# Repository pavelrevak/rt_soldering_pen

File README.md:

# RT soldering pen

![oled4]

[Manual]

This firmware is for my project [RT soldering pen](https://hackaday.io/project/18899-rt-soldering-pen)

You can buy HW at [Tindie](https://www.tindie.com/products/vlk/rt-soldering-pen/)

## Building and flashing

### Requirements

- [`arm-gcc`](https://developer.arm.com/open-source/gnu-toolchain/gnu-rm/downloads)
- [`cmake`](https://cmake.org/download/)
- `make` or [`ninja`](https://github.com/ninja-build/ninja)
- STM flashing SW and HW (ST-Link/V2 or any ST dev-kit, like Discovery or Nucleo board)

Building is possible on Linux, Mac and also on Windows

### Getting source

```sh
git clone --recursive https://github.com/pavelrevak/rt_soldering_pen.git
cd rt_soldering_pen
```

### Building

```sh
mkdir _build
cd _build
cmake -D CMAKE_TOOLCHAIN_FILE=../cmake/arm-none-eabi.cmake -D CMAKE_BUILD_TYPE=Release ..
make
```

### Flashing

Connect ST-Link or other SWD programmer:

#### HW v0.3

- G : GND
- C : SWCLK
- D : SWDIO

#### HW v1.0

- C : SWCLK
- G : GND
- D : SWDIO

If you have installed [pystlink](https://github.com/pavelrevak/pystlink) and is in search path just type:

```sh
make flash
```

If you have another flashing utility you can generate hex of binary file:

```sh
make srec
```

or building also support other targets `hex` and `bin`

Final files are saved in `_build` folder

[manual]: doc/MANUAL.md "Manual"
[oled4]: doc/oled4.png "Screenshot"

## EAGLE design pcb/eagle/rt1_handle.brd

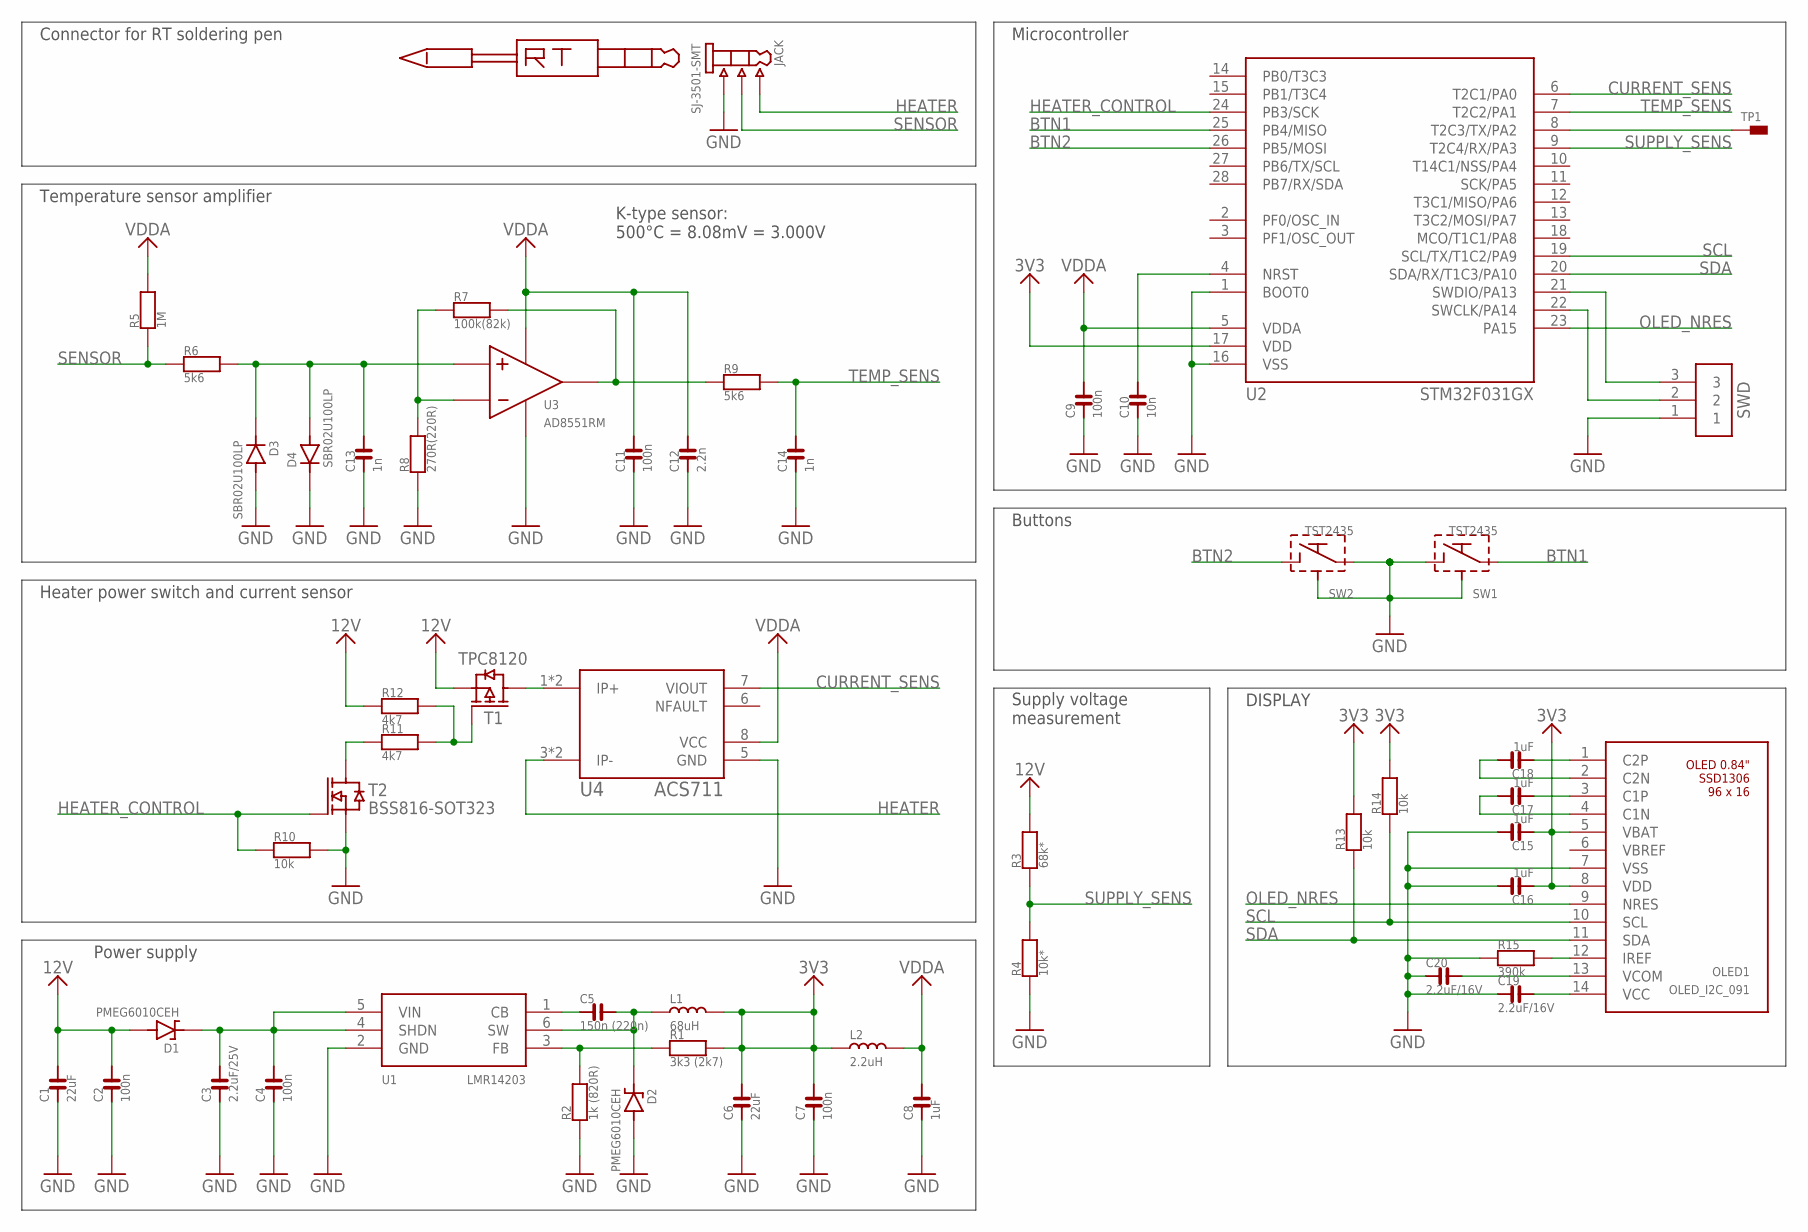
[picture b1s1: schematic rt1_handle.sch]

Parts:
C1: 22uF; 1206
C2, C4, C7, C9, C11: 100n; 0402
C3: 2.2uF/25V; 0805
C5: 150n (220n); 0402
C6: 22uF; 0805
C8, C15, C16, C17, C18: 1uF; 0603
C10: 10n; 0402
C12: 2.2n; 0603
C13, C14: 1n; 0402
C19, C20: 2.2uF/16V; 0603
D1, D2: PMEG6010CEH; SOD123F
D3, D4: SBR02U100LP; DFN1006
JACK: SJ-3501-SMT
L1: 68uH; 1717
L2: 2.2uH; 0805
OLED1: OLED_I2C_091
R1: 3k3 (2k7); 0402
R2: 1k (820R); 0402
R3: 68k*; 0402
R4: 10k*; 0402
R5: 1M; 0402
R6, R9: 5k6; 0402
R7: 100k(82k); 0402
R8: 270R(220R); 0402
R10, R13, R14: 10k; 0402
R11, R12: 4k7; 0402
R15: 390k; 0402
RT: RT-1
SW1, SW2: TST2435
SWD: PINHEAD1X3X; PIN1X3
T1: TPC8120; SOIC8
T2: BSS816-SOT323; SOT23
TP1: TEST_PAD15X60; SMD_15_60
U1: LMR14203; SOT23-6
U2: STM32F031GX; UFQFPN28
U3: AD8551RM; MSOP8
U4: ACS711; SOIC8

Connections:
3V3: C6.2, C7.2, C15.1, C16.1, L1.2, L2.1, OLED1.5 (VBAT), OLED1.8 (VDD), R1.2, R13.2, R14.2, U2.17 (VDD)
12V: C1.2, C2.2, D1.A, R3.2, R12.1, T1.1 (S), T1.2 (S), T1.3 (S)
12V_DC: C3.2, C4.2, D1.C, U1.4 (SHDN), U1.5 (VIN)
BTN1: SW1.1, U2.25 (PB4/MISO)
BTN2: SW2.2, U2.26 (PB5/MOSI)
C1N: C17.2, OLED1.4 (C1N)
C1P: C17.1, OLED1.3 (C1P)
C2N: C18.2, OLED1.2 (C2N)
C2P: C18.1, OLED1.1 (C2P)
CURRENT_SENS: U2.6 (T2C1/PA0), U4.7 (VIOUT)
DEBUG_OUT: TP1.TP, U2.8 (T2C3/TX/PA2)
GND: C1.1, C2.1, C3.1, C4.1, C6.1, C7.1, C8.1, C9.1, C10.1, C11.1, C12.1, C13.1, C14.1, C15.2, C16.2, C19.1, C20.1, D2.A, D3.A, D4.C, JACK.1, JACK.5 (1), OLED1.7 (VSS), R2.1, R4.1, R8.1, R10.2, R15.1, SW1.2, SW1.EP1 (SHIELD), SW1.EP2 (SHIELD), SW2.1, SW2.EP1 (SHIELD), SW2.EP2 (SHIELD), SWD.1, T2.2 (S), U1.2 (GND), U2.1 (BOOT0), U2.16 (VSS), U3.4 (V-), U4.5 (GND)
HEATER: JACK.2, JACK.4 (2), U4.3 (IP-), U4.4 (IP-)
HEATER_CONTROL: R10.1, T2.1 (G), U2.24 (PB3/SCK)
HEATER_PWR: T1.5 (D), T1.6 (D), T1.7 (D), T1.8 (D), U4.1 (IP+), U4.2 (IP+)
IREF: OLED1.12 (IREF), R15.2
NRST: C10.2, U2.4 (NRST)
OLED_NRES: OLED1.9 (NRES), U2.23 (PA15)
POWER_SWITCH: R11.2, R12.2, T1.4 (G)
POWER_SWITCH_LOW: R11.1, T2.3 (D)
SCL: OLED1.10 (SCL), R14.1, U2.19 (SCL/TX/T1C2/PA9)
SDA: OLED1.11 (SDA), R13.1, U2.20 (SDA/RX/T1C3/PA10)
SENSOR: JACK.3, R5.1, R6.1
SENSOR_FEEDBACK: R7.1, R8.2, U3.2 (IN-)
SENSOR_IN: C13.2, D3.C, D4.A, R6.2, U3.3 (IN+)
SENSOR_OUT: R7.2, R9.1, U3.6 (OUT)
SUPPLY_CB: C5.1, U1.1 (CB)
SUPPLY_FB: R1.1, R2.2, U1.3 (FB)
SUPPLY_SENS: R3.1, R4.2, U2.9 (T2C4/RX/PA3)
SWDCLK: SWD.2, U2.22 (SWCLK/PA14)
SWDIO: SWD.3, U2.21 (SWDIO/PA13)
SWOUT: C5.2, D2.C, L1.1, U1.6 (SW)
TEMP_SENS: C14.2, R9.2, U2.7 (T2C2/PA1)
VCC: C19.2, OLED1.14 (VCC)
VCOM: C20.2, OLED1.13 (VCOM)
VDDA: C8.2, C9.2, C11.2, C12.2, L2.2, R5.2, U2.5 (VDDA), U3.7 (V+), U4.8 (VCC)

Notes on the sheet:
K-type sensor: 500°C = 8.08mV = 3.000V
SWD
Power supply
Heater power switch and current sensor
Temperature sensor amplifier
Connector for RT soldering pen
Microcontroller
DISPLAY
Supply voltage measurement
Buttons

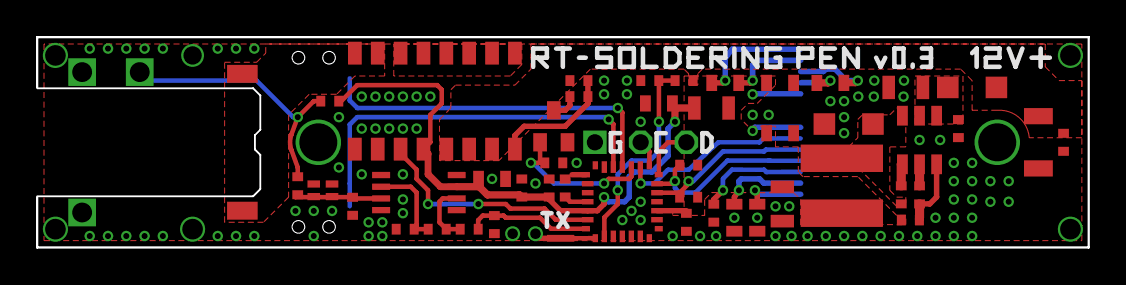
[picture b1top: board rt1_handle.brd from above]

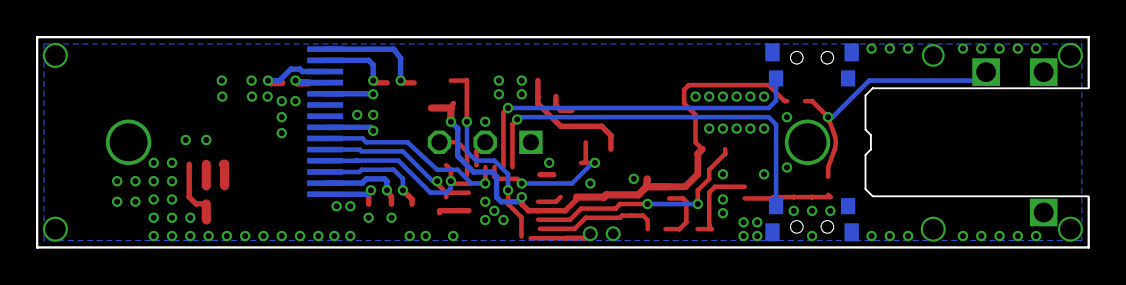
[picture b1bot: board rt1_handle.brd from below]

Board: 2 copper layers, 58.4 x 11.7 mm, 54 parts (3 on the bottom side), 36 nets.

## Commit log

2018-02-24 initial import
2018-03-10 removed pure_virtual_stub, moved button class to lib, moved analog values calculation to board.adc
2018-03-10 removed interrupt for adc dma
2018-03-18 improved handling buttons
2018-03-18 class with presets
2018-05-12 separated screen drawing
2018-05-23 improved naming
2018-05-27 flash using bin (pystlink has small bug with unaligned sections), added cmake target for size
2018-05-30 pragma once
2018-06-16 heating state machine separated from main
2018-06-17 bugfixes - heating is now working
2018-06-17 implemented diagnostics, added docstring
2018-06-17 rearanged code
2018-06-18 added RT TIP diagnostic
2018-06-18 moved heating and preset to src folder
2018-06-18 cleaned preset module
2018-06-18 cleaned screen/main
2018-06-19 fifo docstring update, namespace is lowercase
2018-06-19 updated namespaces
2018-06-20 rewrited stream and printing on display with stringstream
2018-06-20 updated ostream: removed recursive algo, changed types for fonts, ...
2018-06-20 added text width measurement, bugfix in draw_char
2018-06-20 removed unused fonts
2018-06-20 compensated current sensor to increase accuracy
2018-06-20 returned back unused fonts, compiler optimisations remove unused fonts
2018-06-22 support for additional screens
2018-06-22 added info screen
2018-06-22 moved heat processes from main.cpp into heating.hpp
2018-06-22 cleanup
2018-06-22 added io as submodule
2018-06-22 locked submodule to v0.0.20180622
2018-06-23 Create LICENSE
2018-06-23 README
2018-06-28 cleaned board/ADC module
2018-06-29 ADC: code cleaning
2018-06-29 ADC: small code refactoring
2018-06-29 heating: code refactoring and cleaning (no functionality changed)
2018-06-30 moved display init seqeuence into flash
2018-06-30 optimized drawing of info screen (this code need to rework)
2018-06-30 added undervoltage limit to limit heating power if batery has too low voltage (actually is set to 4.3V)
2018-06-30 working versions are marked with '+' like v0.0.1+
2018-06-30 added watchdog
2018-07-01 add magic word before framebuffer to easy find framebuffer in memory and take screenshots
2018-07-02 optimalized FIFO for 2^n items
2018-07-02 fixed issue with current compensation
2018-07-05 removed debugging (not used actually, can be added later, if needed)
2018-07-06 added manual
2018-07-06 corrected naming of variables with to
2018-07-06 moved manual into doc
2018-07-06 added screenshots
2018-07-06 updated doc with screenshots
2018-07-07 added simple script for creating screenshots over SWD/StLink debugger
2018-07-08 screenshot generator: configurable border
2018-07-11 improved info screen handling
2018-07-11 other improvement of info screen handling
2018-07-12 added script for testing buttons on HW without connected display
2018-07-13 fixed long buttons press
2018-07-21 basic support for Fahrenheits, one block of FLASH memory used as nonvolatile for settings with vear leveling optimizations, optimized info screen, added option to swtich degree F or C
2018-07-23 added option for advanced screen, now is default screen simple (show only preset and measured temperature) and switching to advanced screen is by menu option
2018-07-24 left-handed mode
2018-07-24 renamed info screen to menu
2018-07-24 updated documentation
2018-07-24 updated doc
2018-07-24 increased version to v0.1.0
2018-07-27 reduced binary size by removing unused fonts and unused characters (size is reduced for about 2KB)
2018-07-29 Updated manual
2018-07-29 linker script for 16KB MCU
2018-07-29 detecting shortcut on RT TIP (this state is still not processed to protect RT tip)
2018-08-03 new version of io
2018-08-03 updated Readme.md (clone with recursive)
2018-08-07 increased current limit for heater from 6A to 9A, now it will work at 18V supply
2018-08-08 updated .gitignore
2018-08-08 added minmax library
2018-08-08 added overheat limit (to 500 degree Celsius), in case of overheat will be immediatelly switched into standby + dissable heating if is standby mode
2018-08-08 increased minimum set-point temperature to 50 degree C, use minmax lib, added const to methods and code cleaning
2018-08-08 heating: added const, removed unused constant
2018-08-08 show overheat info on display (in simple mode show OH)
2018-08-08 rewrited PID, changed some modifications of PID and changed constants, now is faster heating, smaller overshot, faster reaction during soldering, .. but there is still room for improvements
2018-08-08 simple mode: in standby if temperature is more than 50 degree Celsius will temperature blink
2018-08-09 saving preset temperatures
2018-08-09 v0.2.0
2018-08-12 added used eagle libraries
2018-08-12 added schematic pdf + renamed folder
2018-08-12 pdf: schematic + pcb
2018-09-03 fixed warnings Wconversion, Wold-style-cast and Wcast-align
2018-09-03 fixed warnings Wsign-conversion
2018-09-03 fixed warnings Wshadow
2018-09-03 fixed warnings Wlogical-op
2018-09-03 updated version v0.2.0+
2018-09-04 fixed warnings Wsuggest-override
2018-09-07 removed unnecessary .cpp files
2018-09-07 updated io
2018-09-08 added dependencies comments into screenshot maker
2018-09-08 better power bargraph in simple main screen
2018-10-19 added missing mosfet library
2019-01-09 updated io to new version
2019-01-09 bugfixes for gcc-8
2019-09-22 added support for HW v1.0 (with automatic detection HW revision) + update to new io
2019-09-26 v0.3.0
2019-10-05 renamed screen ID INFO to MENU
2019-10-05 added Thermocouple type-D characteristic
2019-10-05 updated buttons testing script to exit when both buttons are pressed longer than 1s
2019-10-06 increased temperature range for HW v1.0
2019-10-06 Display control improvemenets - Display DIM after 2 minutes after inactivity - Display OFF after 15 minutes - Settings for higher brightness
2019-10-06 added schematic for hw v1.0
2019-10-06 added TOOD
2019-10-06 v0.4.0
2020-03-09 moved flash to drv
2020-03-09 updated names for constants
2020-03-09 added missing include
2020-03-09 moved eagle folder
2020-03-09 moved watchdog to drv
2021-01-20 Add "high power" setting
    Adds new selectable menu item to settings that is a boolean "high power" setting. When off, this will limit power output via heating.hpp to 40W. When on, it will limit power output via heating.hpp to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
2021-01-20 Add High Power menu item
    Adds a selectable boolean setting called "high power" beneath the "left handed" menu item. Changing this in the menu will modify the HIGH_POWER setting in settings.hpp to allow either 40W (false) or 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
2021-01-20 Update power output bar for RTU
    Added if statement to change scale of power output bar if using RTU tip (150W limit instead of 40W)
2021-01-20 Add Tip Type and allow for variable max power
    Added new enum for TipType
    Added function to calculate tip type based on heater resistance
    Added max power calculation in init function to account for either menu setting or determined tip type (that part requires more work)
2021-01-23 Revert "Update power output bar for RTU"
2021-01-23 Update heating.hpp
    Modification to pid constant initialization. Moved from init() to start() so that it actively checks for tip type change and adjusts max power in real time. Also commented out code for manual power l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
2021-01-23 Allow high power
    Added class for TipType (RTM, RTU, Unknown)
    Added code to determine tip type based on resistance
    Added code to account for new low and high resistance in tip heater status
    Added code to start() to select appropriate max power based on tip type and send it to pid constants call
    Moved pid constant setting from init() to start() so that max power gets updated in real time
2021-01-23 Modify power bar for 150W
    Added code to power output bar to account for 150W output if using RTU tip
2021-01-23 Removed unnecessary high power settings check
    Removed code that checked for high power setting in start(). If power will be set by menu instead of automatically, this will not be needed, and if power is set automatically instead of manually, thi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
2021-01-23 Corrected syntax error in start()
    Removed extra } in if/else statement for tip type
2021-01-23 Cleaned up style
2021-01-28 Add new maximum voltage
    New maximum voltage constant added. Now there are two, one for RTM tips (14V) and one for RTU tips (25V).
2021-01-28 Added second max voltage
    Now there is one maximum voltage for RTM (14V) and one for RTU (25V) tips. Currently RTU tip limit is set to 25V due to the input capacitor limit of HW1.0.
2021-01-28 Force Tip Type to Unknown
    Added line to start() that forces _tip_type to TipType::UNKNOWN with the rest of the variable initialization. This forces the iron to limit max output power to 150mW until a tip type is determined (R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
2021-01-29 Adds high power
    Automatically detects tip type (RTM vs. RTU) and applies appropriate maximum power during _start() process (either 40W or 150W). If tip type is unknown, max power is 150mW for safety.
    Currently, "150W" setting is limited to 15W in order to test without risk of destroying anything until code is verified to work correctly.
2021-01-29 Modify power output bar
    Changed code so that power output bar properly scales when max power is 150W instead of 40W.
